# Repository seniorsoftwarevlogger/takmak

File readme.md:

# Takmak — No Compromise 65% Split Keyboard

[Сайт и сборка](https://seniorsoftwarevlogger.github.io/takmak/) · [Студия ракурсов](https://seniorsoftwarevlogger.github.io/takmak/studio.html)

Сплит-клавиатура с полной русской раскладкой, включая «Ъ», и минимумом изменений
привычного расположения. Низкий и стандартный профили корпуса, универсальная
плата для обеих половинок, варианты кнопок и энкодеров.

Такмак — скала рядом с Красноярском. Её топография нанесена на шелкографию платы
и используется в оформлении сайта.

## Что лежит в репозитории

| Каталог | Содержание |
| --- | --- |
| `scene/` | Сайт, интерактивная 3D-сцена, студия ракурсов и файлы для скачивания |
| `3d models/step/` | Актуальные STEP-экспорты корпусов, reset-кнопок и крутилок |
| `3d models/Takmak/`, `3d models/Encoder Knob 16mm 3mm/` | Исходные GLB-экспорты |
| `3d models/*.stl`, `3d models/low profile/` | Более ранние модели из GitHub; не заменяют актуальные STEP |
| `kicad/` | Универсальная PCB 3.1, схема и проект |
| `Takmak-left/` | Более ранние проекты отдельной левой платы |
| `gerber/` | Сохранённые Gerber-файлы из прежней версии репозитория; ревизия требует сверки |
| `firmware/` | Снимки ZMK-модуля Takmak, модуля экрана донгла и исторических вариантов |
| `qmk_firmware/`, `zmk_firmware/` | Исторические конфигурации; не готовые прошивки для всех современных сборок |
| `assets/` | Фотография, исходная топография DXF и выбранные ракурсы |
| `docs/` | Инвентаризация и история проекта |

Полные деревья ZMK/Zephyr и локальные каталоги сборок сюда не копируются:
в `firmware/` сохранены относящиеся к Takmak модули и конфигурации, зависимости
основного модуля закреплены в его `config/west.yml`.

## Ревизии и сборка

**3.0** — последняя изготовленная плата. **3.1** добавляет посадки под Choc
hotswap и пока не изготовлена. Gerber-файлы в `gerber/` исторические: они пока
не сопоставлены с текущей схемой и не выдаются за производственный комплект 3.1.
Недостающие проверенные производственные архивы и инструкции добавим позднее.

На одну клавиатуру автор указал:

- 2 × SuperMini nRF52840 или другие контроллеры, совместимые с nice!nano;
- 2 × EEMB 383454LC LiPo, 3,7 В, 720 мА·ч, с JST;
- Choc v1/v2 либо MX-совместимые свитчи с подходящими кейкапами;
- EC11 с нажатием; правый энкодер опционален;
- OLED 0,91″, 128×32, I²C на левой половинке.

По одному контроллеру и аккумулятору на половинку. Отдельный донгл добавляется
при выборе такой конфигурации. Полный BOM, карта пайки и проверенные UF2 ещё
готовятся. [Текущий порядок сборки](scene/public/downloads/takmak-assembly.md).

## Разработка сайта

Node.js 24 и Python 3:

```sh
npm ci --prefix scene
npm --prefix scene run dev
```

Проверка и сборка для GitHub Pages:

```sh
npm --prefix scene run check
python3 scene/scripts/prepare-downloads.py
PAGES_BASE_PATH=/takmak/ npm --prefix scene run build
python3 scene/scripts/verify-site.py /takmak/
```

Workflow `.github/workflows/pages.yml` проверяет PR и публикует `scene/dist`
при push в `master`. В Settings → Pages выбран источник **GitHub Actions**.
Локальная разработка работает от `/`, публикация — от `/takmak/`.

## История и использование

[Видео проекта](https://www.youtube.com/watch?v=rlwhCginQdo) · [Исходная раскладка](http://www.keyboard-layout-editor.com/#/gists/c3e709013b8413fe901a2af3728c1977)

You may not use this for any commercial purpose.

Это исходное ограничение аппаратного проекта. У модулей прошивки и сторонних
компонентов свои лицензии, сохранённые рядом с ними. Более ранний README
сохранён в `docs/archive/github-readme-before-consolidation.md`.

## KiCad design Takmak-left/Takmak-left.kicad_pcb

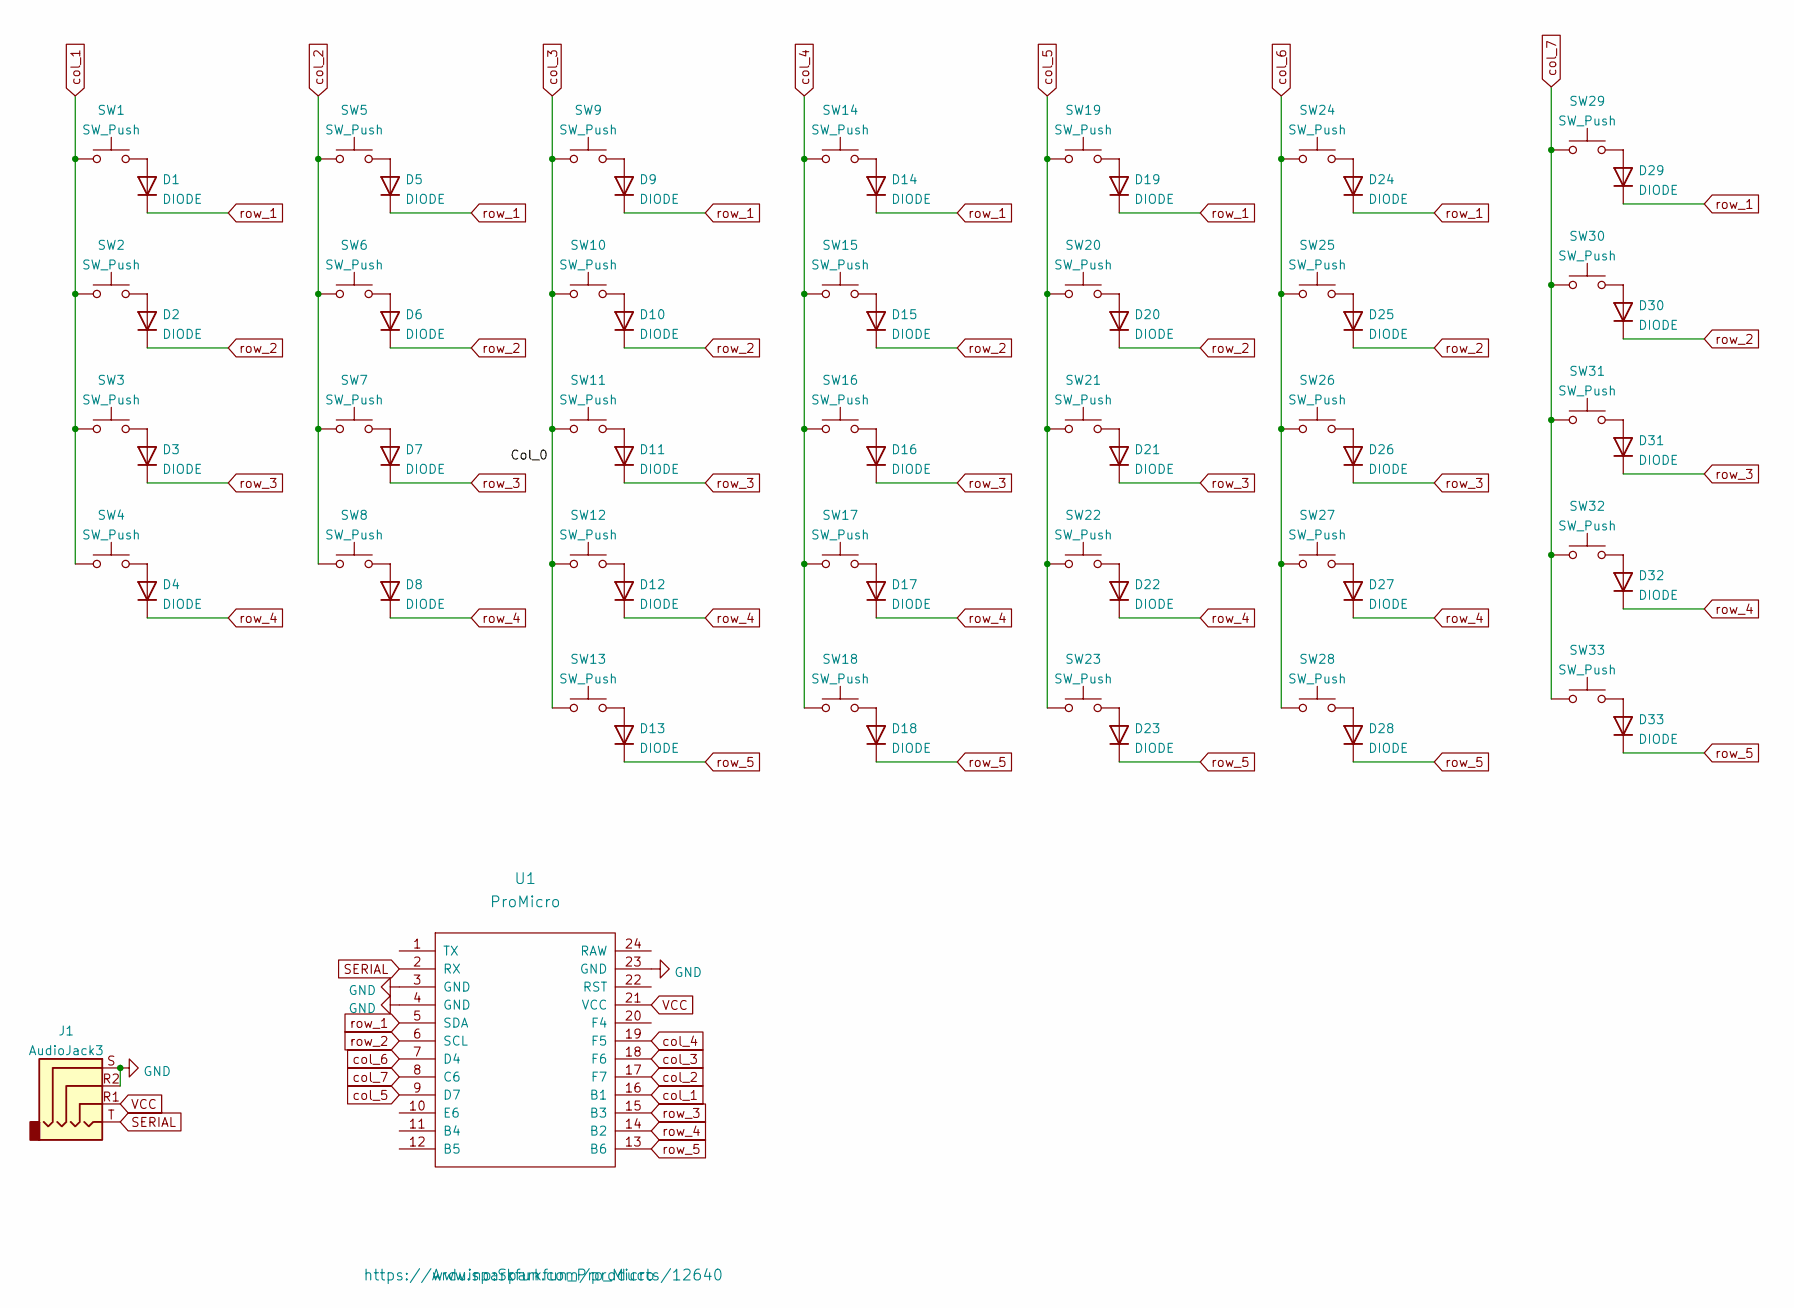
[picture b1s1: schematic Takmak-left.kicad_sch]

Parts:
D1, D2, D3, D4, D5, D6, D7, D8, D9, D10, D11, D12, D13, D14, D15, D16, D17, D18, D19, D20, D21, D22, D23, D24, D25, D26, D27, D28, D29, D30, D31, D32, D33: DIODE; D_DO-35_SOD27_P7.62mm_Horizontal
J1: AudioJack3; TRRS-PJ-320A
SW1, SW2, SW3, SW4, SW5, SW6, SW7, SW8, SW9, SW10, SW11, SW12, SW13, SW14, SW15, SW16, SW17, SW18, SW19, SW20, SW21, SW22, SW23, SW24, SW25, SW26, SW27, SW28, SW29, SW30, SW31, SW32, SW33: SW_Push; SW_MX_PG1350
U1: ProMicro; Sparkfun_Pro_Micro

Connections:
GND: J1.R2, J1.S, U1.3 (GND), U1.4 (GND), U1.23 (GND)
unnamed: D1.2 (A), SW1.2
unnamed: D2.2 (A), SW2.2
unnamed: D3.2 (A), SW3.2
unnamed: D4.2 (A), SW4.2
unnamed: D5.2 (A), SW5.2
unnamed: D6.2 (A), SW6.2
unnamed: D7.2 (A), SW7.2
unnamed: D8.2 (A), SW8.2
unnamed: D9.2 (A), SW9.2
unnamed: D10.2 (A), SW10.2
unnamed: D11.2 (A), SW11.2
unnamed: D12.2 (A), SW12.2
unnamed: D13.2 (A), SW13.2
unnamed: D14.2 (A), SW14.2
unnamed: D15.2 (A), SW15.2
unnamed: D16.2 (A), SW16.2
unnamed: D17.2 (A), SW17.2
unnamed: D18.2 (A), SW18.2
unnamed: D19.2 (A), SW19.2
unnamed: D20.2 (A), SW20.2
unnamed: D21.2 (A), SW21.2
unnamed: D22.2 (A), SW22.2
unnamed: D23.2 (A), SW23.2
unnamed: D24.2 (A), SW24.2
unnamed: D25.2 (A), SW25.2
unnamed: D26.2 (A), SW26.2
unnamed: D27.2 (A), SW27.2
unnamed: D28.2 (A), SW28.2
unnamed: D29.2 (A), SW29.2
unnamed: D30.2 (A), SW30.2
unnamed: D31.2 (A), SW31.2
unnamed: D32.2 (A), SW32.2
unnamed: D33.2 (A), SW33.2
SERIAL: J1.T, U1.2 (RX)
col_1: SW1.1, SW2.1, SW3.1, SW4.1, U1.16 (B1)
col_2: SW5.1, SW6.1, SW7.1, SW8.1, U1.17 (F7)
col_3: SW9.1, SW10.1, SW11.1, SW12.1, SW13.1, U1.18 (F6)
col_4: SW14.1, SW15.1, SW16.1, SW17.1, SW18.1, U1.19 (F5)
col_5: SW19.1, SW20.1, SW21.1, SW22.1, SW23.1, U1.9 (D7)
col_6: SW24.1, SW25.1, SW26.1, SW27.1, SW28.1, U1.7 (D4)
col_7: SW29.1, SW30.1, SW31.1, SW32.1, SW33.1, U1.8 (C6)
row_1: D1.1 (K), D5.1 (K), D9.1 (K), D14.1 (K), D19.1 (K), D24.1 (K), D29.1 (K), U1.5 (SDA)
row_2: D2.1 (K), D6.1 (K), D10.1 (K), D15.1 (K), D20.1 (K), D25.1 (K), D30.1 (K), U1.6 (SCL)
row_3: D3.1 (K), D7.1 (K), D11.1 (K), D16.1 (K), D21.1 (K), D26.1 (K), D31.1 (K), U1.15 (B3)
row_4: D4.1 (K), D8.1 (K), D12.1 (K), D17.1 (K), D22.1 (K), D27.1 (K), D32.1 (K), U1.14 (B2)
row_5: D13.1 (K), D18.1 (K), D23.1 (K), D28.1 (K), D33.1 (K), U1.13 (B6)

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
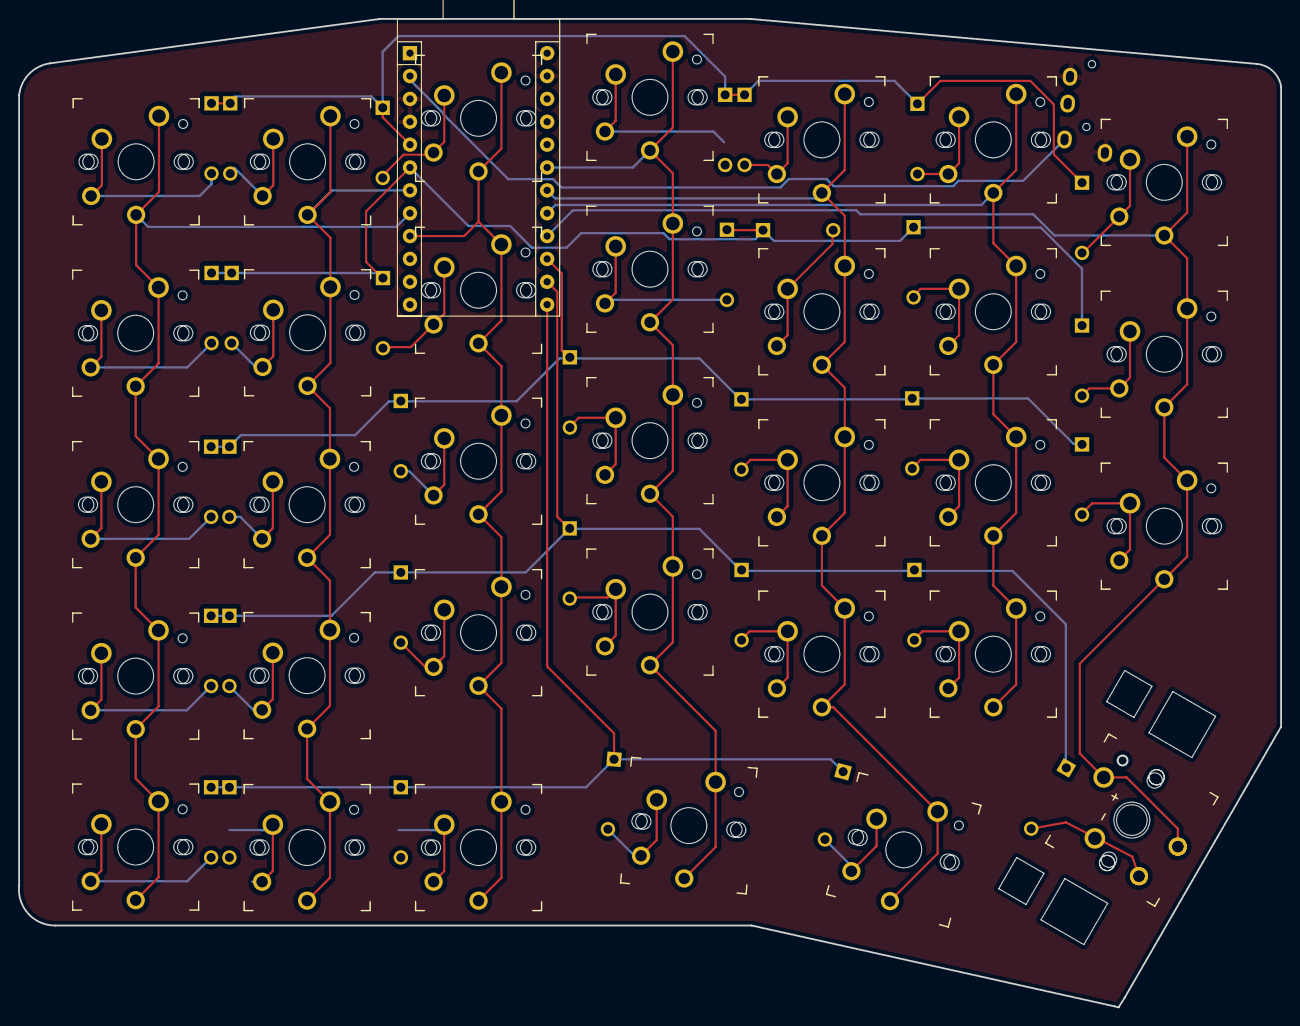
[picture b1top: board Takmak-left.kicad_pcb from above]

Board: 2 copper layers, 140.3 x 109.8 mm, 68 parts (1 on the bottom side), 47 nets.

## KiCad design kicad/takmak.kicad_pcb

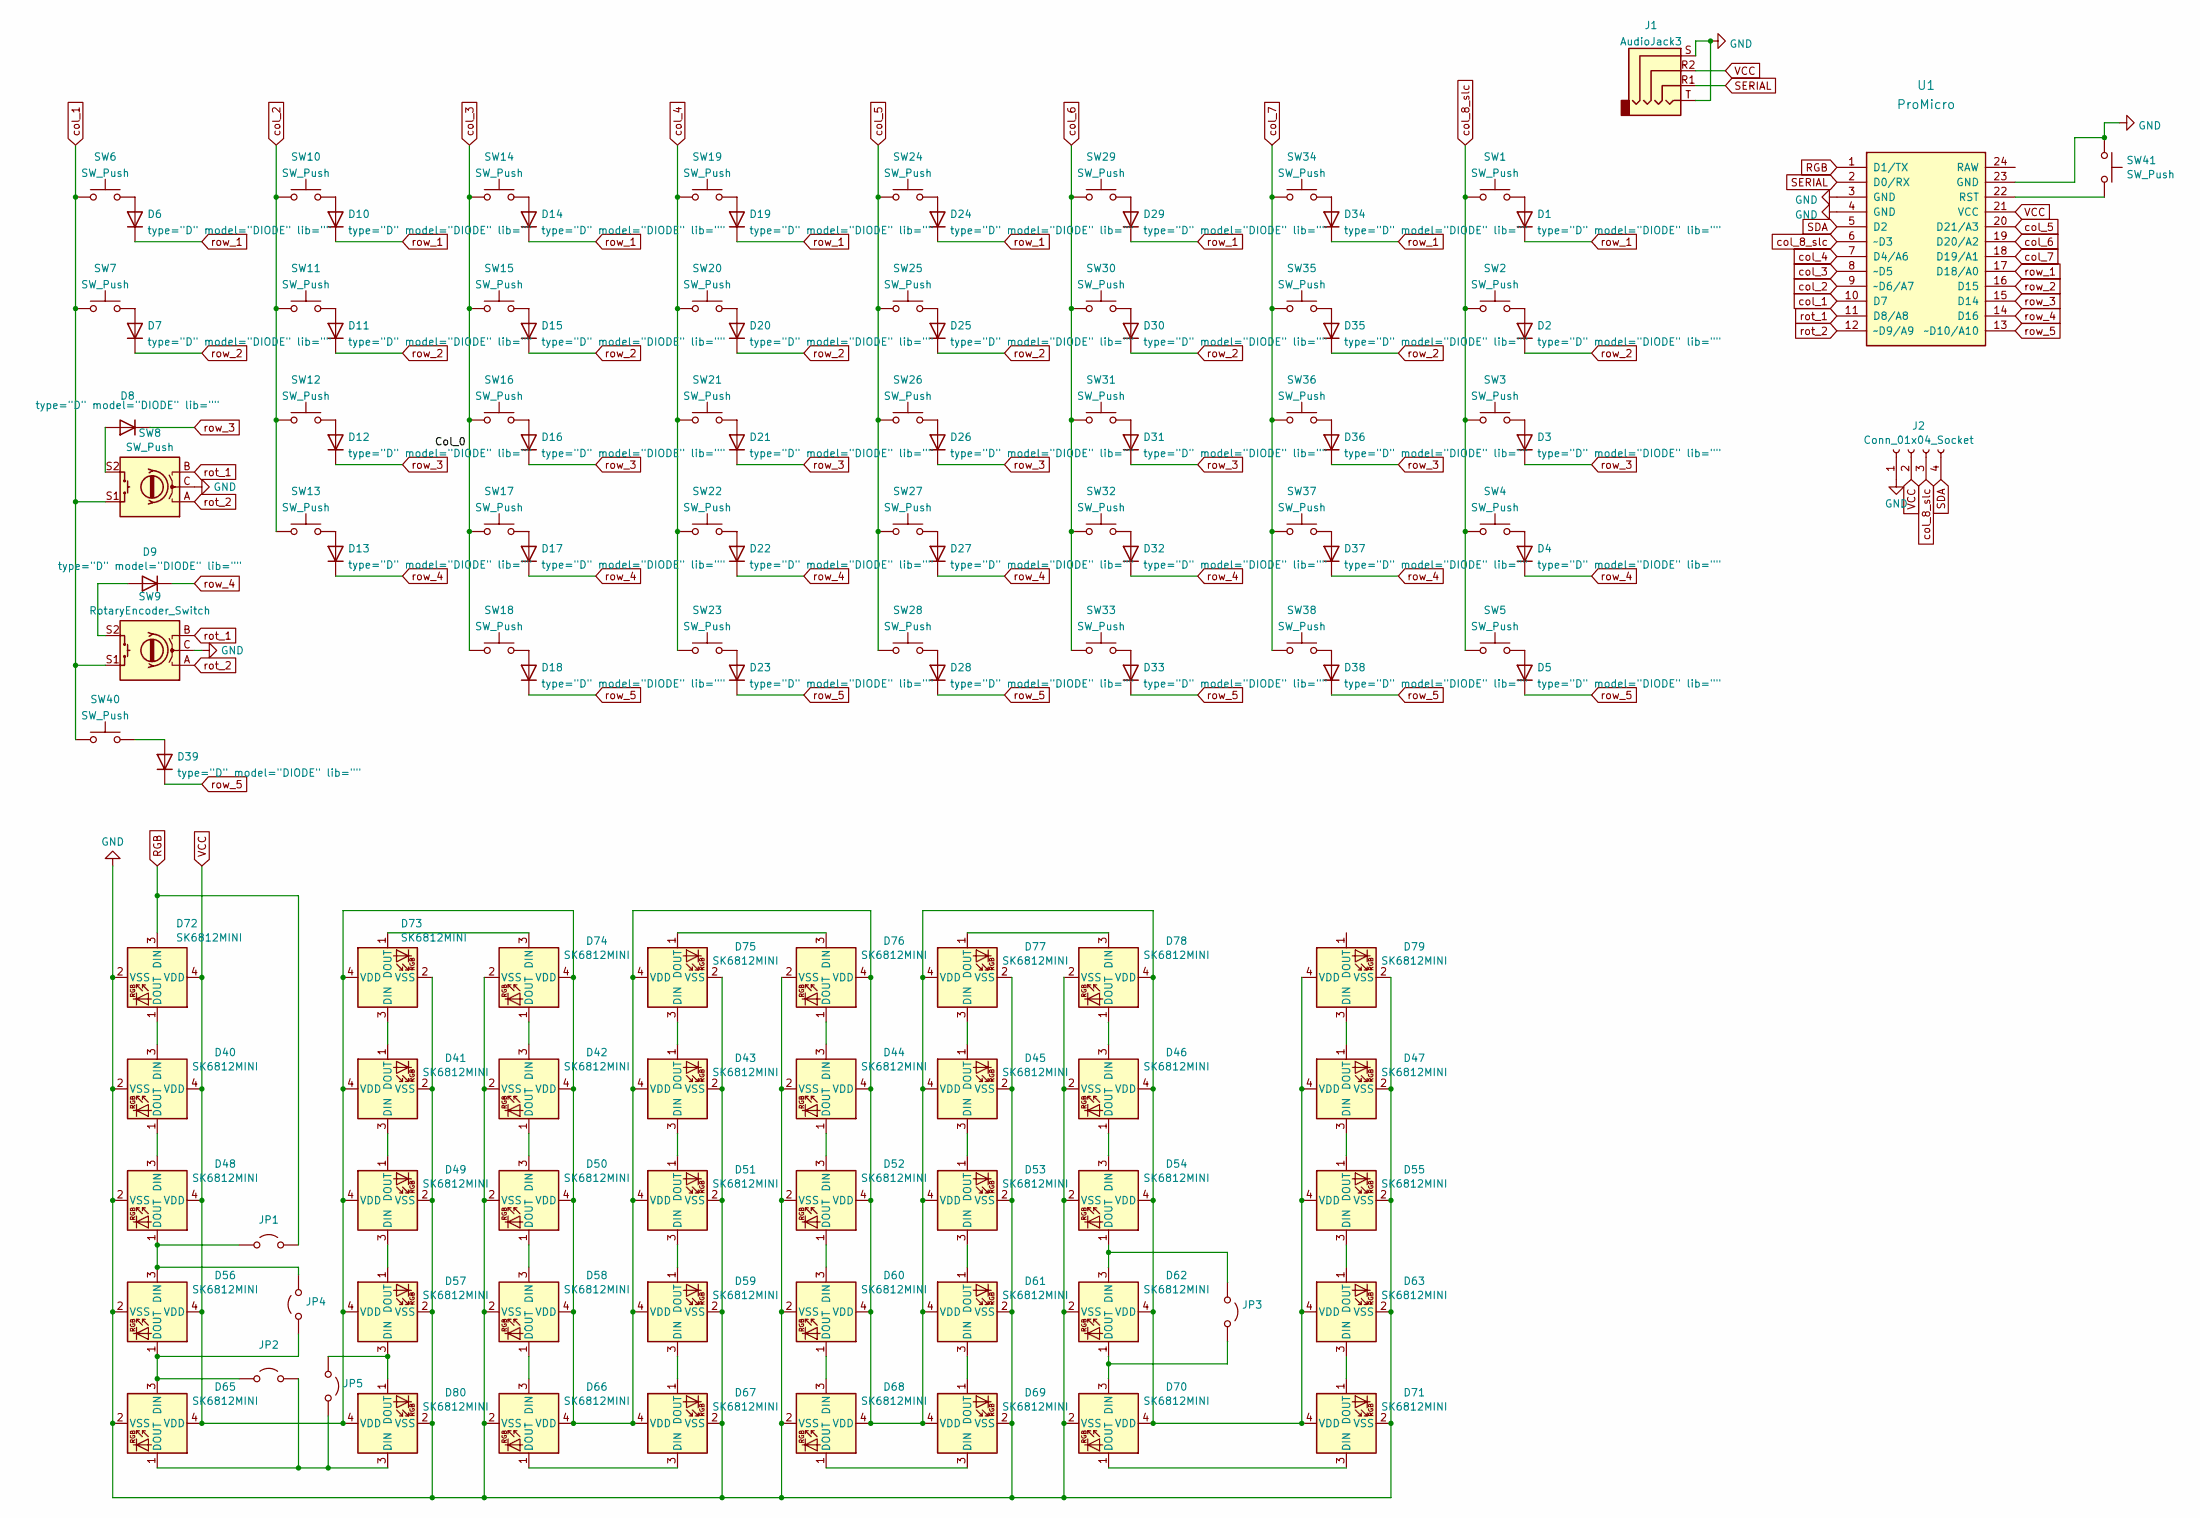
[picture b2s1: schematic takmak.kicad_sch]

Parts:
D1, D2, D3, D4, D5, D6, D7, D8, D9, D10, D11, D12, D13, D14, D15, D16, D17, D18, D19, D20, D21, D22, D23, D24, D25, D26, D27, D28, D29, D30, D31, D32, D33, D34, D35, D36, D37, D38, D39: type="D" model="DIODE" lib=""; D_DO-35_SOD27_P7.62mm_Horizontal
D40, D41, D42, D43, D44, D45, D46, D47, D48, D49, D50, D51, D52, D53, D54, D55, D56, D57, D58, D59, D60, D61, D62, D63, D65, D66, D67, D68, D69, D70, D71, D72, D73, D74, D75, D76, D77, D78, D79, D80: SK6812MINI; LED_SK6812MINI_PLCC4_3.5x3.5mm_P1.75mm
J1: AudioJack3; TRRS-PJ-320A
J2: Conn_01x04_Socket; I2C_Breakout
JP1, JP2, JP3, JP4, JP5: (no value)
SW1, SW2, SW3, SW4, SW5, SW6, SW7, SW10, SW11, SW12, SW13, SW14, SW15, SW16, SW17, SW18, SW19, SW20, SW21, SW22, SW23, SW24, SW25, SW26, SW27, SW28, SW29, SW30, SW31, SW32, SW33, SW34, SW35, SW36, SW37, SW38, SW40: SW_Push; SW_MX_PG1350
SW8: SW_Push; MX_Kailh_EC11
SW9: RotaryEncoder_Switch; RotaryEncoder_EC11-no-legs
SW41: SW_Push; SW_Tactile_SPST_NO_Straight_CK_PTS636Sx25SMTRLFS
U1: ProMicro; Sparkfun_Pro_Micro

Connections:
GND: D40.2 (VSS), D41.2 (VSS), D42.2 (VSS), D43.2 (VSS), D44.2 (VSS), D45.2 (VSS), D46.2 (VSS), D47.2 (VSS), D48.2 (VSS), D49.2 (VSS), D50.2 (VSS), D51.2 (VSS), D52.2 (VSS), D53.2 (VSS), D54.2 (VSS), D55.2 (VSS), D56.2 (VSS), D57.2 (VSS), D58.2 (VSS), D59.2 (VSS), D60.2 (VSS), D61.2 (VSS), D62.2 (VSS), D63.2 (VSS), D65.2 (VSS), D66.2 (VSS), D67.2 (VSS), D68.2 (VSS), D69.2 (VSS), D70.2 (VSS), D71.2 (VSS), D72.2 (VSS), D73.2 (VSS), D74.2 (VSS), D75.2 (VSS), D76.2 (VSS), D77.2 (VSS), D78.2 (VSS), D79.2 (VSS), D80.2 (VSS), J1.S, J1.T, J2.1, SW8.C, SW9.C, SW41.1, U1.3 (GND), U1.4 (GND), U1.23 (GND); also elsewhere on the board
unnamed: D1.2 (A), SW1.2
unnamed: D2.2 (A), SW2.2
unnamed: D3.2 (A), SW3.2
unnamed 4: D4.2 (A), SW4.2; also elsewhere on the board
unnamed: D5.2 (A), SW5.2
unnamed: D6.2 (A), SW6.2
unnamed: D7.2 (A), SW7.2
unnamed: D8.2 (A), SW8.S2
unnamed: D9.2 (A), SW9.S2
unnamed: D10.2 (A), SW10.2
unnamed: D11.2 (A), SW11.2
unnamed: D12.2 (A), SW12.2
unnamed: D13.2 (A), SW13.2
unnamed: D14.2 (A), SW14.2
unnamed: D15.2 (A), SW15.2
unnamed: D16.2 (A), SW16.2
unnamed: D17.2 (A), SW17.2
unnamed: D18.2 (A), SW18.2
unnamed: D19.2 (A), SW19.2
unnamed: D20.2 (A), SW20.2
unnamed: D21.2 (A), SW21.2
unnamed: D22.2 (A), SW22.2
unnamed: D23.2 (A), SW23.2
unnamed: D24.2 (A), SW24.2
unnamed: D25.2 (A), SW25.2
unnamed: D26.2 (A), SW26.2
unnamed: D27.2 (A), SW27.2
unnamed: D28.2 (A), SW28.2
unnamed: D29.2 (A), SW29.2
unnamed: D30.2 (A), SW30.2
unnamed: D31.2 (A), SW31.2
unnamed: D32.2 (A), SW32.2
unnamed: D33.2 (A), SW33.2
unnamed: D34.2 (A), SW34.2
unnamed: D35.2 (A), SW35.2
unnamed: D36.2 (A), SW36.2
unnamed: D37.2 (A), SW37.2
unnamed: D38.2 (A), SW38.2
unnamed: D39.2 (A), SW40.2
unnamed: D40.3 (DIN), D72.1 (DOUT)
unnamed: D40.1 (DOUT), D48.3 (DIN)
unnamed: D41.3 (DIN), D49.1 (DOUT)
unnamed: D41.1 (DOUT), D73.3 (DIN)
unnamed: D42.3 (DIN), D74.1 (DOUT)
unnamed: D42.1 (DOUT), D50.3 (DIN)
unnamed: D43.3 (DIN), D51.1 (DOUT)
unnamed: D43.1 (DOUT), D75.3 (DIN)
unnamed: D44.3 (DIN), D76.1 (DOUT)
unnamed: D44.1 (DOUT), D52.3 (DIN)
unnamed: D45.3 (DIN), D53.1 (DOUT)
unnamed: D45.1 (DOUT), D77.3 (DIN)
unnamed: D46.3 (DIN), D78.1 (DOUT)
unnamed: D46.1 (DOUT), D54.3 (DIN)
unnamed: D47.3 (DIN), D55.1 (DOUT)
unnamed: D47.1 (DOUT), D79.3 (DIN)
unnamed: D48.1 (DOUT), D56.3 (DIN), JP1.1 (A), JP4.2 (B)
unnamed: D49.3 (DIN), D57.1 (DOUT)
unnamed: D50.1 (DOUT), D58.3 (DIN)
unnamed: D51.3 (DIN), D59.1 (DOUT)
unnamed: D52.1 (DOUT), D60.3 (DIN)
unnamed: D53.3 (DIN), D61.1 (DOUT)
unnamed: D54.1 (DOUT), D62.3 (DIN), JP3.1 (A)
unnamed 63: D55.3 (DIN), D63.1 (DOUT); also elsewhere on the board
unnamed: D56.1 (DOUT), D65.3 (DIN), JP2.1 (A), JP4.1 (A)
unnamed: D57.3 (DIN), D80.1 (DOUT), JP5.1 (A)
unnamed: D58.1 (DOUT), D66.3 (DIN)
unnamed: D59.3 (DIN), D67.1 (DOUT)
unnamed: D60.1 (DOUT), D68.3 (DIN)
unnamed: D61.3 (DIN), D69.1 (DOUT)
unnamed: D62.1 (DOUT), D70.3 (DIN), JP3.2 (B)
unnamed 71: D63.3 (DIN), D71.1 (DOUT); also elsewhere on the board
unnamed: D65.1 (DOUT), D80.3 (DIN), JP2.2 (B), JP5.2 (B)
unnamed: D66.1 (DOUT), D67.3 (DIN)
unnamed: D68.1 (DOUT), D69.3 (DIN)
unnamed: D70.1 (DOUT), D71.3 (DIN)
unnamed: D73.1 (DOUT), D74.3 (DIN)
unnamed: D75.1 (DOUT), D76.3 (DIN)
unnamed: D77.1 (DOUT), D78.3 (DIN)
unnamed: SW41.2, U1.22 (RST)
RGB: D72.3 (DIN), JP1.2 (B), U1.1 (D1/TX)
SDA: J2.4, U1.5 (D2); also elsewhere on the board
SERIAL: J1.R1, U1.2 (D0/RX)
VCC: D40.4 (VDD), D41.4 (VDD), D42.4 (VDD), D43.4 (VDD), D44.4 (VDD), D45.4 (VDD), D46.4 (VDD), D47.4 (VDD), D48.4 (VDD), D49.4 (VDD), D50.4 (VDD), D51.4 (VDD), D52.4 (VDD), D53.4 (VDD), D54.4 (VDD), D55.4 (VDD), D56.4 (VDD), D57.4 (VDD), D58.4 (VDD), D59.4 (VDD), D60.4 (VDD), D61.4 (VDD), D62.4 (VDD), D63.4 (VDD), D65.4 (VDD), D66.4 (VDD), D67.4 (VDD), D68.4 (VDD), D69.4 (VDD), D70.4 (VDD), D71.4 (VDD), D72.4 (VDD), D73.4 (VDD), D74.4 (VDD), D75.4 (VDD), D76.4 (VDD), D77.4 (VDD), D78.4 (VDD), D79.4 (VDD), D80.4 (VDD), J1.R2, J2.2, U1.21 (VCC); also elsewhere on the board
col_1: SW6.1, SW7.1, SW8.S1, SW9.S1, SW40.1, U1.10 (D7)
col_2: SW10.1, SW11.1, SW12.1, SW13.1, U1.9 (~D6/A7)
col_3: SW14.1, SW15.1, SW16.1, SW17.1, SW18.1, U1.8 (~D5)
col_4: SW19.1, SW20.1, SW21.1, SW22.1, SW23.1, U1.7 (D4/A6)
col_5: SW24.1, SW25.1, SW26.1, SW27.1, SW28.1, U1.20 (D21/A3)
col_6: SW29.1, SW30.1, SW31.1, SW32.1, SW33.1, U1.19 (D20/A2)
col_7: SW34.1, SW35.1, SW36.1, SW37.1, SW38.1, U1.18 (D19/A1)
col_8_slc: J2.3, SW1.1, SW2.1, SW3.1, SW4.1, SW5.1, U1.6 (~D3); also elsewhere on the board
rot_1: SW8.B, SW9.B, U1.11 (D8/A8)
rot_2: SW8.A, SW9.A, U1.12 (~D9/A9)
row_1: D1.1 (K), D6.1 (K), D10.1 (K), D14.1 (K), D19.1 (K), D24.1 (K), D29.1 (K), D34.1 (K), U1.17 (D18/A0)
row_2: D2.1 (K), D7.1 (K), D11.1 (K), D15.1 (K), D20.1 (K), D25.1 (K), D30.1 (K), D35.1 (K), U1.16 (D15)
row_3: D3.1 (K), D8.1 (K), D12.1 (K), D16.1 (K), D21.1 (K), D26.1 (K), D31.1 (K), D36.1 (K), U1.15 (D14)
row_4: D4.1 (K), D9.1 (K), D13.1 (K), D17.1 (K), D22.1 (K), D27.1 (K), D32.1 (K), D37.1 (K), U1.14 (D16)
row_5: D5.1 (K), D18.1 (K), D23.1 (K), D28.1 (K), D33.1 (K), D38.1 (K), D39.1 (K), U1.13 (~D10/A10)

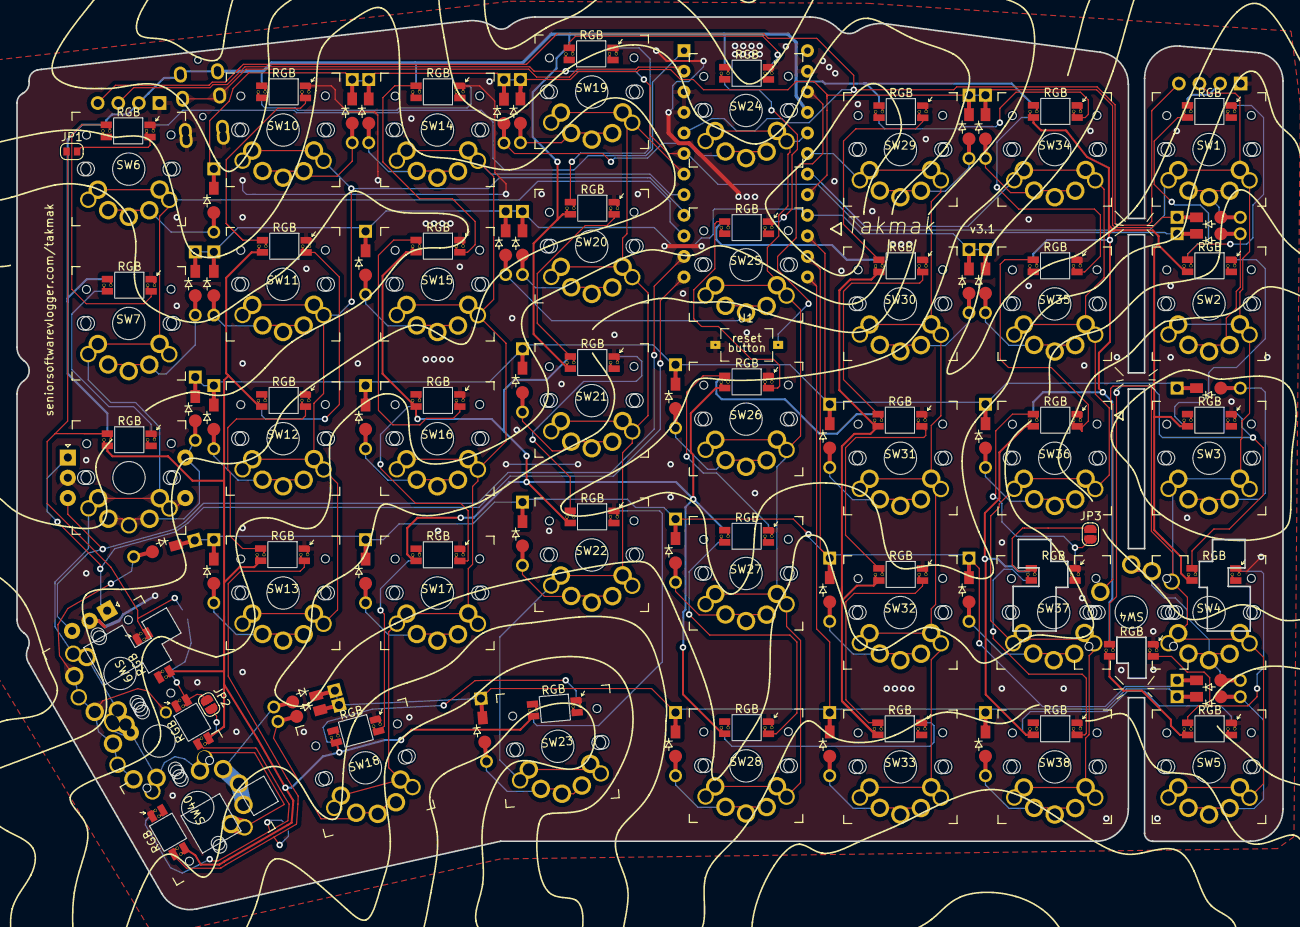
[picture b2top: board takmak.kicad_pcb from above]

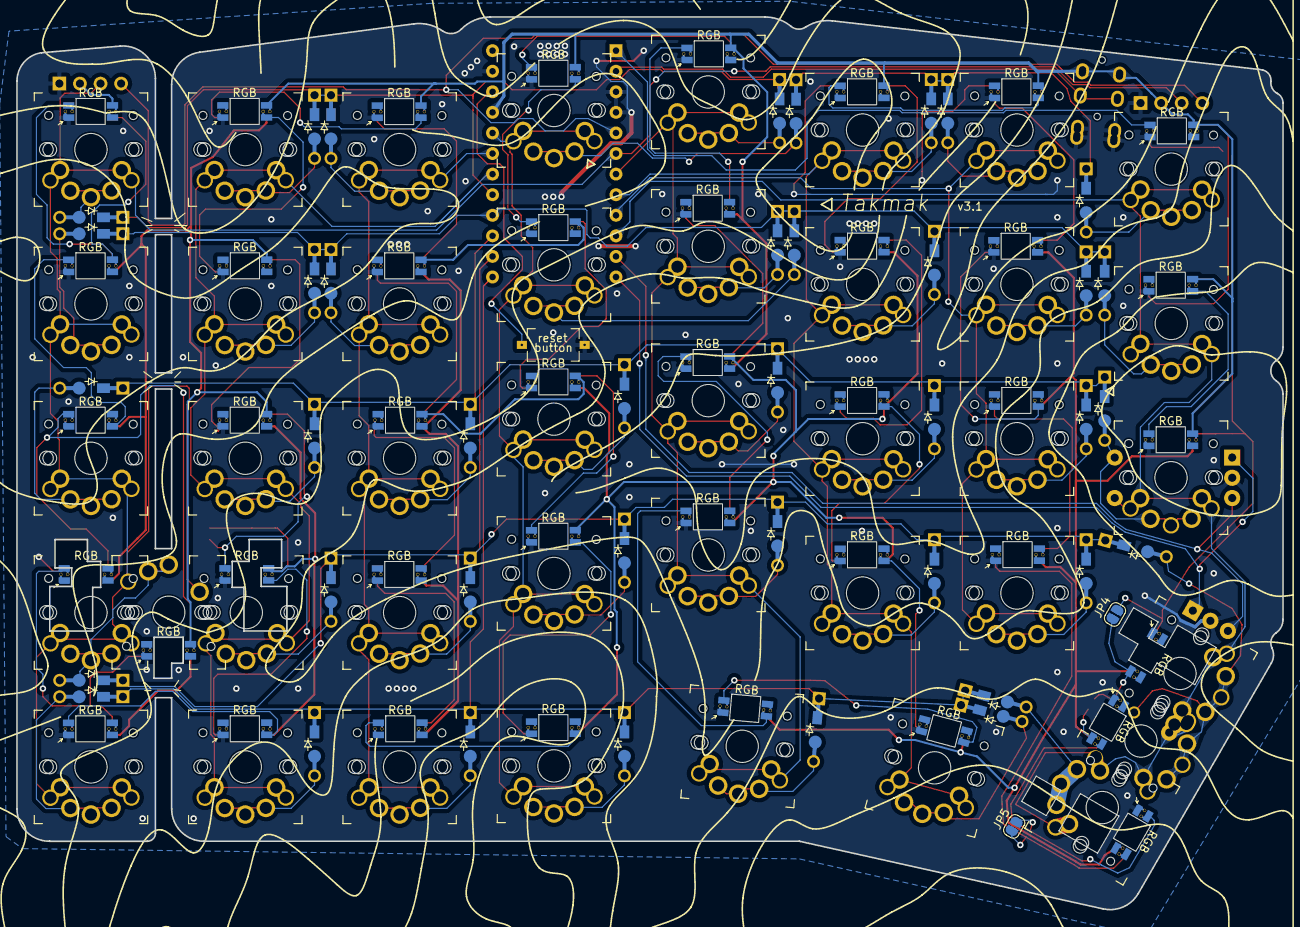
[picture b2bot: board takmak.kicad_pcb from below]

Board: 2 copper layers, 156.3 x 110.2 mm, 131 parts (3 on the bottom side), 99 nets.

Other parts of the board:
D63#2: SK6812MINI; SK68XXMini_1
J2#2: Conn_01x04_Socket; I2C_Breakout
Kailh PG1350: Choc; Kailh-PG1350-2u-Stab
SW4#2: SW_Push; MX-Choc-Double

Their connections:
GND: D63#2.2 (VSS), J2#2.1; also elsewhere on the board
unnamed 4: SW4#2.2; also elsewhere on the board
unnamed 63: D63#2.1 (DOUT); also elsewhere on the board
unnamed 71: D63#2.3 (DIN); also elsewhere on the board
SDA: J2#2.4; also elsewhere on the board
VCC: D63#2.4 (VDD), J2#2.2; also elsewhere on the board
col_8_slc: J2#2.3, SW4#2.1; also elsewhere on the board

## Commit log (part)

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2021-02-04 init
2021-02-07 add mouse keys
2022-02-03 ssv_split -> takmak
2022-02-03 Add PCB matrix
2022-02-03 move ESC instead of CAPS
2022-03-19 Create scheme
2022-11-13 Add gerber files
2022-11-13 Add ZMK config
2022-11-14 Add qmk config
2022-11-14 Add low profile case
